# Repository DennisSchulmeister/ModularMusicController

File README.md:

Modular Music Controller
========================

<p align="center">
   <!-- https://pixabay.com/photos/screwdriver-background-screw-wooden-1008974/ -->
   
   <br>
   <b>Under Construction</b>
   <br>
   This is not yet ready for production. Many features are still missing!
   <br>
   Leave a star on GitHub and send us a message to stay updated.
</p>

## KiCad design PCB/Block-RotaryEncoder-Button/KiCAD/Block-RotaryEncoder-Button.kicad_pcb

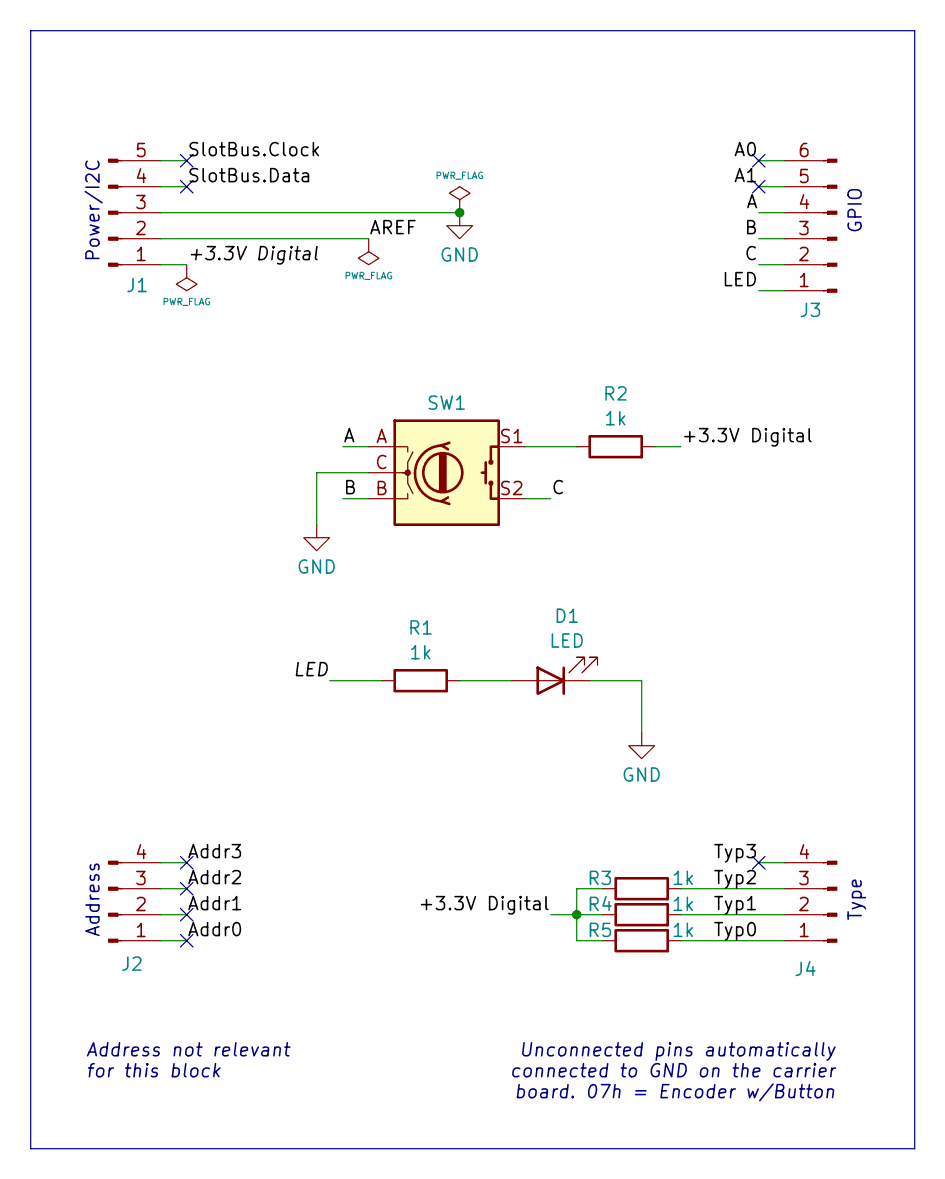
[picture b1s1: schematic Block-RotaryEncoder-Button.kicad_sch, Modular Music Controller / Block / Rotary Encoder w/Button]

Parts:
D1: LED; LED_0805_2012Metric
J1: Samtec MTMS-105-02-T-S-100; PinHeader_1x05_P1.27mm_Vertical
J2, J4: Samtec MTMS-104-02-T-S-100; PinHeader_1x04_P1.27mm_Vertical
J3: Samtec MTMS-106-02-T-S-100; PinHeader_1x06_P1.27mm_Vertical
R1, R2, R3, R4, R5: 1k; R_0402_1005Metric
SW1: CTS 11CEK25F243B; RotaryEncoder_Alps_EC11E-Switch_Vertical_H20mm

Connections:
/+3.3V Digital: J1.1, R2.2, R3.1, R4.1, R5.1
/A: J3.4, SW1.A
/A0: J3.6
/A1: J3.5
/AREF: J1.2
/Addr0: J2.1
/Addr1: J2.2
/Addr2: J2.3
/Addr3: J2.4
/B: J3.3, SW1.B
/C: J3.2, SW1.S2
/LED: J3.1, R1.1
/SlotBus.Clock: J1.5
/SlotBus.Data: J1.4
/Typ0: J4.1, R5.2
/Typ1: J4.2, R4.2
/Typ2: J4.3, R3.2
/Typ3: J4.4
GND: D1.1 (K), J1.3, SW1.C
unnamed: D1.2 (A), R1.2
unnamed: R2.1, SW1.S1

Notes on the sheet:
Unconnected pins automatically connected to GND on the carrier board. 07h = Encoder w/Button
GPIO
Type
Address not relevant for this block
Address
Power/I2C

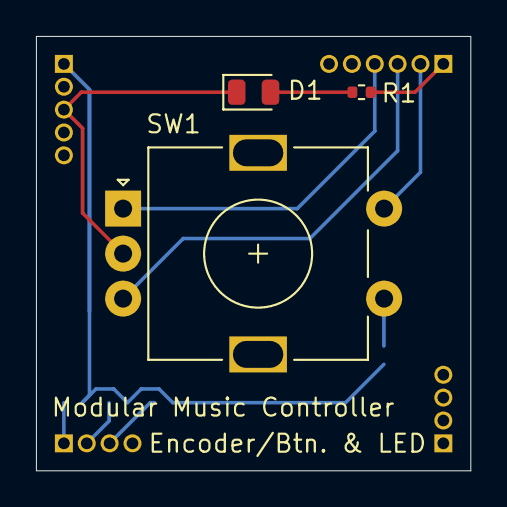
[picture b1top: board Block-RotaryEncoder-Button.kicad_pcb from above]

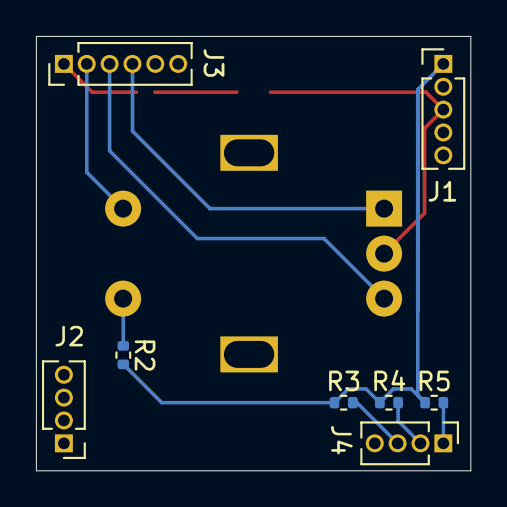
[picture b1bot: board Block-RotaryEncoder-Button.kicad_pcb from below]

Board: 2 copper layers, 24.1 x 24.1 mm, 11 parts (8 on the bottom side), 11 nets.

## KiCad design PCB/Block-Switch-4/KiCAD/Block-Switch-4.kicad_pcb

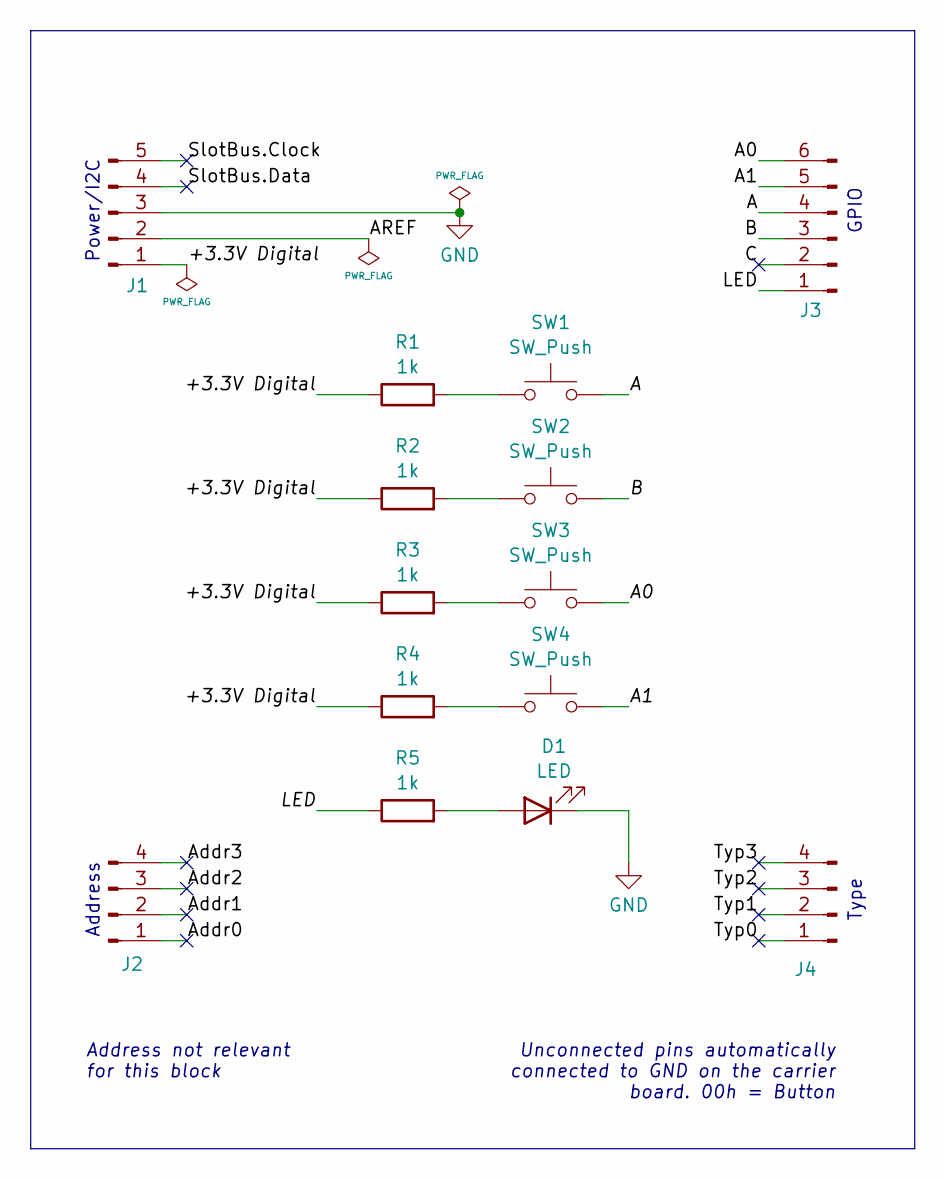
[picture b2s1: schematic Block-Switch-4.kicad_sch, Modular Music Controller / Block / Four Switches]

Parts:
D1: LED; LED_0805_2012Metric
J1: Samtec MTMS-105-02-T-S-100; PinHeader_1x05_P1.27mm_Vertical
J2, J4: Samtec MTMS-104-02-T-S-100; PinHeader_1x04_P1.27mm_Vertical
J3: Samtec MTMS-106-02-T-S-100; PinHeader_1x06_P1.27mm_Vertical
R1, R2, R3, R4, R5: 1k; R_0402_1005Metric
SW1, SW2, SW3, SW4: SW_Push; SW_PUSH_6mm

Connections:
/+3.3V Digital: J1.1, R1.1, R2.1, R3.1, R4.1
/A: J3.4, SW1.2
/A0: J3.6, SW3.2
/A1: J3.5, SW4.2
/AREF: J1.2
/Addr0: J2.1
/Addr1: J2.2
/Addr2: J2.3
/Addr3: J2.4
/B: J3.3, SW2.2
/C: J3.2
/LED: J3.1, R5.1
/SlotBus.Clock: J1.5
/SlotBus.Data: J1.4
/Typ0: J4.1
/Typ1: J4.2
/Typ2: J4.3
/Typ3: J4.4
GND: D1.1 (K), J1.3
unnamed: D1.2 (A), R5.2
unnamed: R1.2, SW1.1
unnamed: R2.2, SW2.1
unnamed: R3.2, SW3.1
unnamed: R4.2, SW4.1

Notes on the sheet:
Unconnected pins automatically connected to GND on the carrier board. 00h = Button
GPIO
Type
Address not relevant for this block
Address
Power/I2C

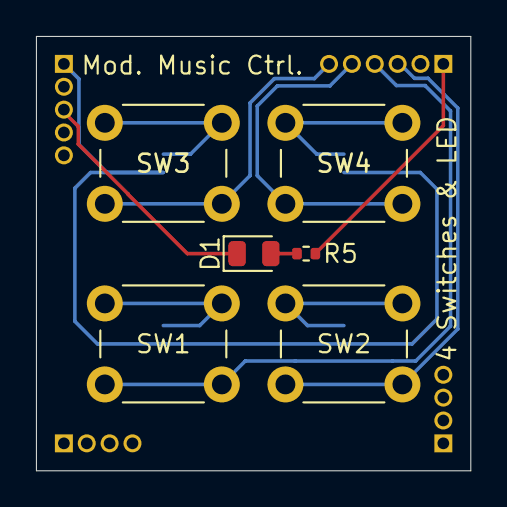
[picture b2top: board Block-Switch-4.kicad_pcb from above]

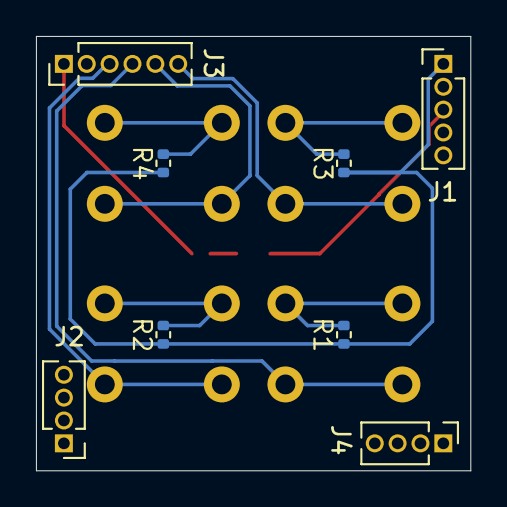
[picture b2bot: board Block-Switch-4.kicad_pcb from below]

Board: 2 copper layers, 24.1 x 24.1 mm, 14 parts (8 on the bottom side), 12 nets.

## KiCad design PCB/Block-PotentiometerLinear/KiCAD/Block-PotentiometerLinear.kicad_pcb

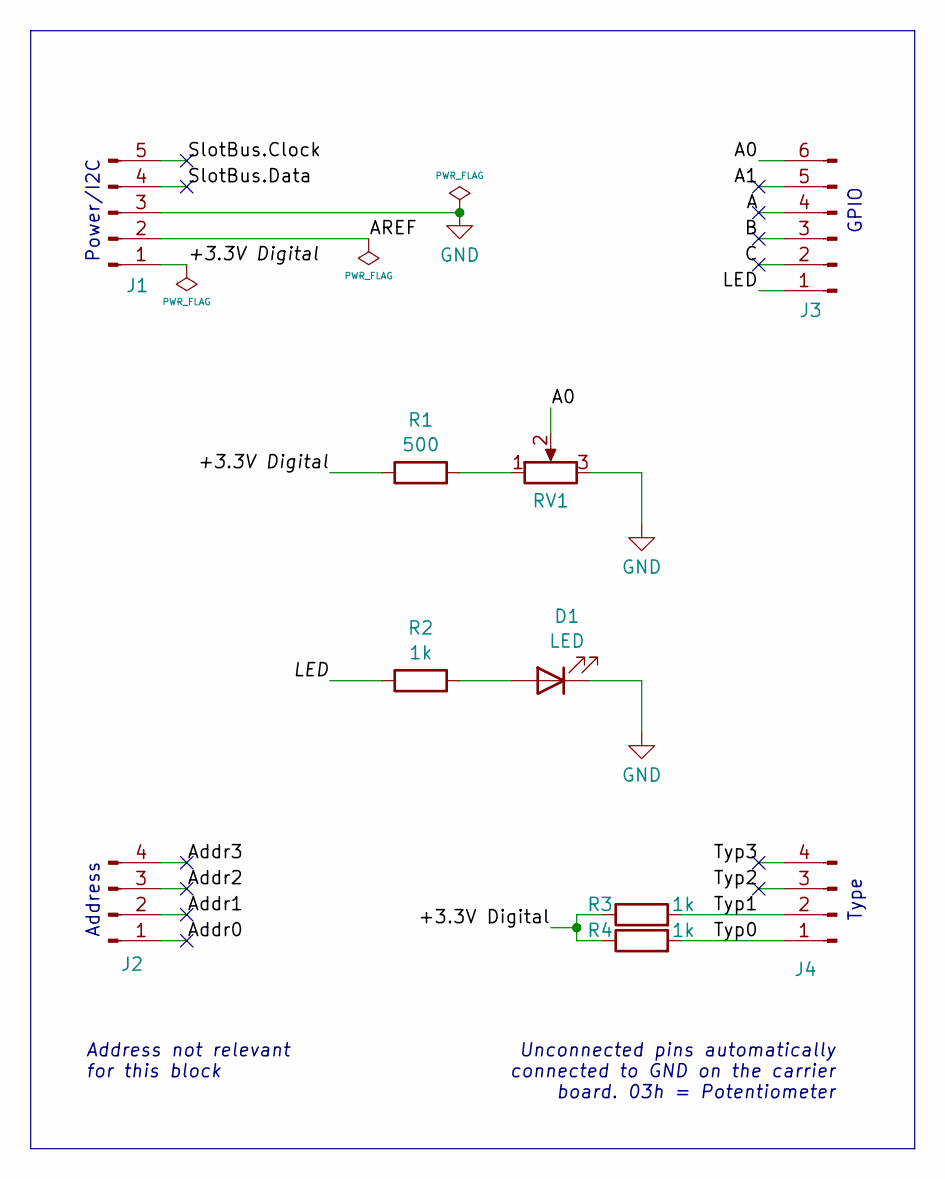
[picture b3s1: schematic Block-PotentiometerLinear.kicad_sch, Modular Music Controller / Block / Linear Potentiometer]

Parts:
D1: LED; LED_0805_2012Metric
J1: Samtec MTMS-105-02-T-S-100; PinHeader_1x05_P1.27mm_Vertical
J2, J4: Samtec MTMS-104-02-T-S-100; PinHeader_1x04_P1.27mm_Vertical
J3: Samtec MTMS-106-02-T-S-100; PinHeader_1x06_P1.27mm_Vertical
R1: 500; R_0402_1005Metric
R2, R3, R4: 1k; R_0402_1005Metric
RV1: Alps Alpine RK09D1130A1N; Potentiometer_Alps_RK09K_Single_Vertical

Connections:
/+3.3V Digital: J1.1, R1.1, R3.1, R4.1
/A: J3.4
/A0: J3.6, RV1.2
/A1: J3.5
/AREF: J1.2
/Addr0: J2.1
/Addr1: J2.2
/Addr2: J2.3
/Addr3: J2.4
/B: J3.3
/C: J3.2
/LED: J3.1, R2.1
/SlotBus.Clock: J1.5
/SlotBus.Data: J1.4
/Typ0: J4.1, R4.2
/Typ1: J4.2, R3.2
/Typ2: J4.3
/Typ3: J4.4
GND: D1.1 (K), J1.3, RV1.3
unnamed: D1.2 (A), R2.2
unnamed: R1.2, RV1.1

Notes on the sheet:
Unconnected pins automatically connected to GND on the carrier board. 03h = Potentiometer
GPIO
Type
Address not relevant for this block
Address
Power/I2C

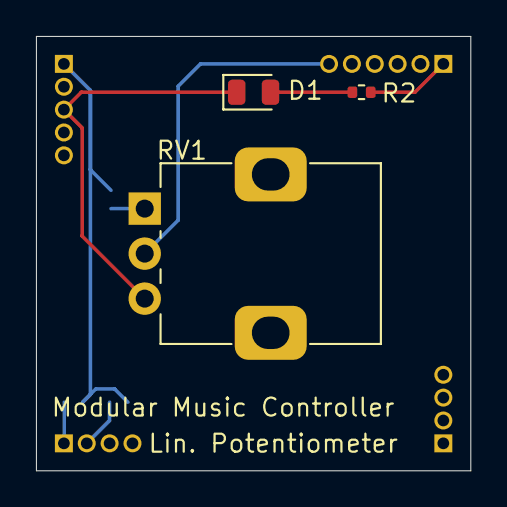
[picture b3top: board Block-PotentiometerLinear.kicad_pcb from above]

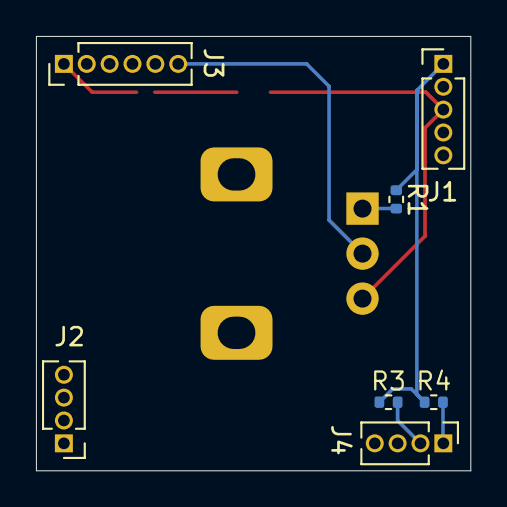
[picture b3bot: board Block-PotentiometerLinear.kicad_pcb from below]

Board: 2 copper layers, 24.1 x 24.1 mm, 10 parts (7 on the bottom side), 8 nets.

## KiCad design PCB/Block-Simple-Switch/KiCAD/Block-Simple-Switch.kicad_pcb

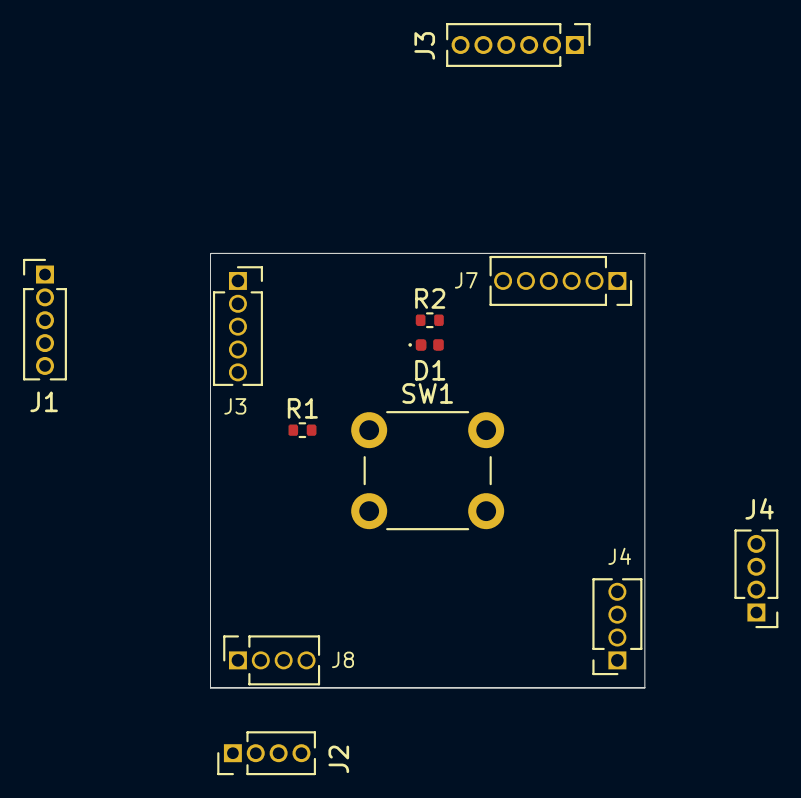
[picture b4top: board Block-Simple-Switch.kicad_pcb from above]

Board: 2 copper layers, 24.1 x 24.1 mm, 12 parts (0 on the bottom side), 6 nets, no tracks yet.

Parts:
D1: LED; LED_0402_1005Metric
J1: Samtec MTMS-105-02-T-S-100; PinHeader_1x05_P1.27mm_Vertical
J2, J4: Samtec MTMS-104-02-T-S-100; PinHeader_1x04_P1.27mm_Vertical
J3: Samtec RSM-105-02-L-S; PinSocket_1x05_P1.27mm_Vertical
J3#2: Samtec MTMS-106-02-T-S-100; PinHeader_1x06_P1.27mm_Vertical
J4#2, J8: Samtec RSM-104-02-L-S; PinSocket_1x04_P1.27mm_Vertical
J7: Samtec RSM-106-02-L-S; PinSocket_1x06_P1.27mm_Vertical
R1, R2: 1k; R_0402_1005Metric
SW1: SW_Push; SW_PUSH_6mm

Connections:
/+3.3V Digital: J1.1, R1.1
/A: J3#2.4, SW1.2
/LED: J3#2.1, R2.1
GND: D1.1 (K), J1.3, J3.3
unnamed: D1.2 (A), R2.2
unnamed: R1.2, SW1.1

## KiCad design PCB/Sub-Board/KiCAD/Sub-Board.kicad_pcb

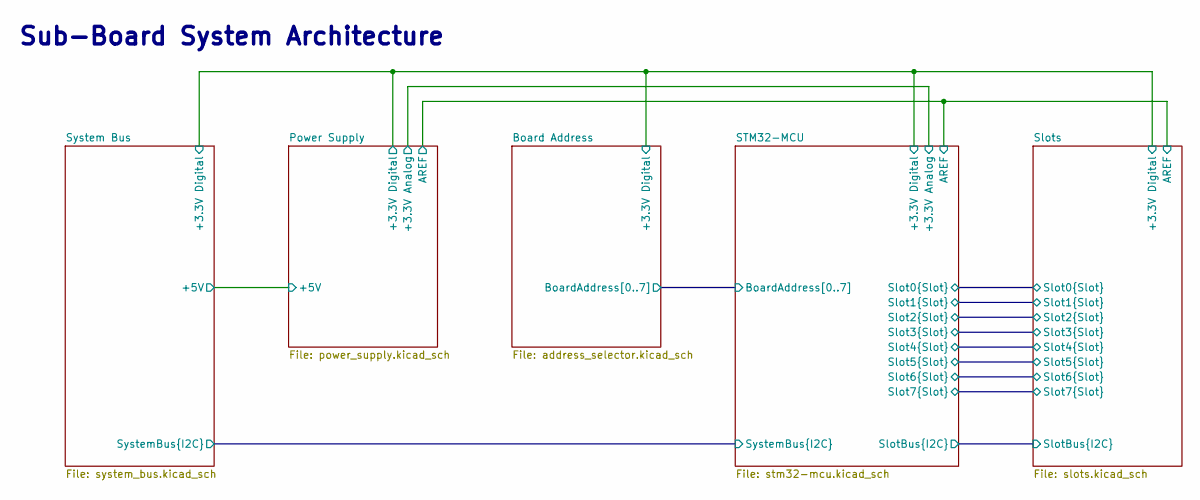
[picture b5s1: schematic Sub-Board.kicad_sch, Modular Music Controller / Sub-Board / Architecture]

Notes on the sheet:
Sub-Board System Architecture

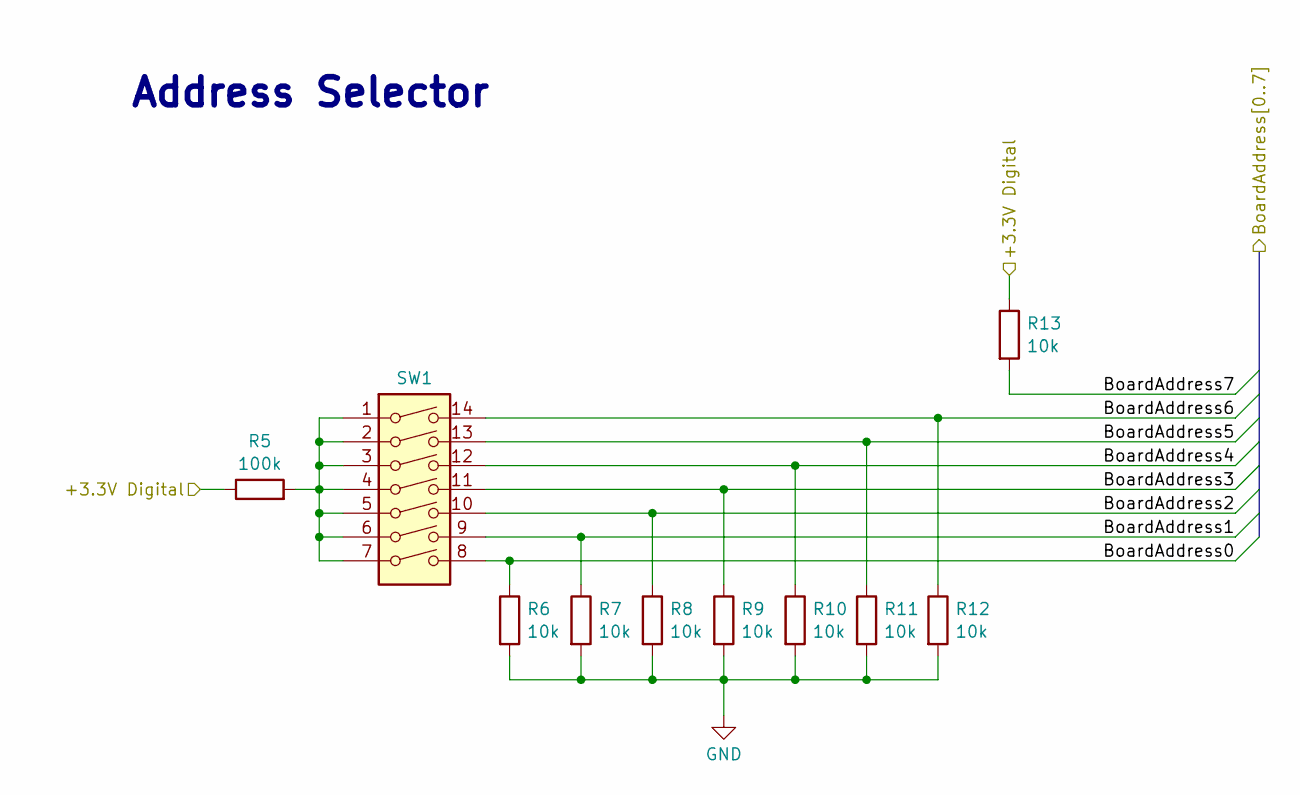
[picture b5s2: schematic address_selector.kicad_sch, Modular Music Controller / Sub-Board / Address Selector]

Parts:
R5: 100k; R_0402_1005Metric
R6, R7, R8, R9, R10, R11, R12, R13: 10k; R_0402_1005Metric
SW1: CTS 219-7LPSTR; SW_DIP_SPSTx07_Slide_6.7x19.34mm_W6.73mm_P2.54mm_LowProfile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

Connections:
/Board Address/+3.3V Digital: R5.1, R13.1; also elsewhere on the board
/Board Address/BoardAddress0: R6.1, SW1.8; also elsewhere on the board
/Board Address/BoardAddress1: R7.1, SW1.9; also elsewhere on the board
/Board Address/BoardAddress2: R8.1, SW1.10; also elsewhere on the board
/Board Address/BoardAddress3: R9.1, SW1.11; also elsewhere on the board
/Board Address/BoardAddress4: R10.1, SW1.12; also elsewhere on the board
/Board Address/BoardAddress5: R11.1, SW1.13; also elsewhere on the board
/Board Address/BoardAddress6: R12.1, SW1.14; also elsewhere on the board
/Board Address/BoardAddress7: R13.2; also elsewhere on the board
GND: R6.2, R7.2, R8.2, R9.2, R10.2, R11.2, R12.2; also elsewhere on the board
unnamed: R5.2, SW1.1, SW1.2, SW1.3, SW1.4, SW1.5, SW1.6, SW1.7

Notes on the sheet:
Address Selector

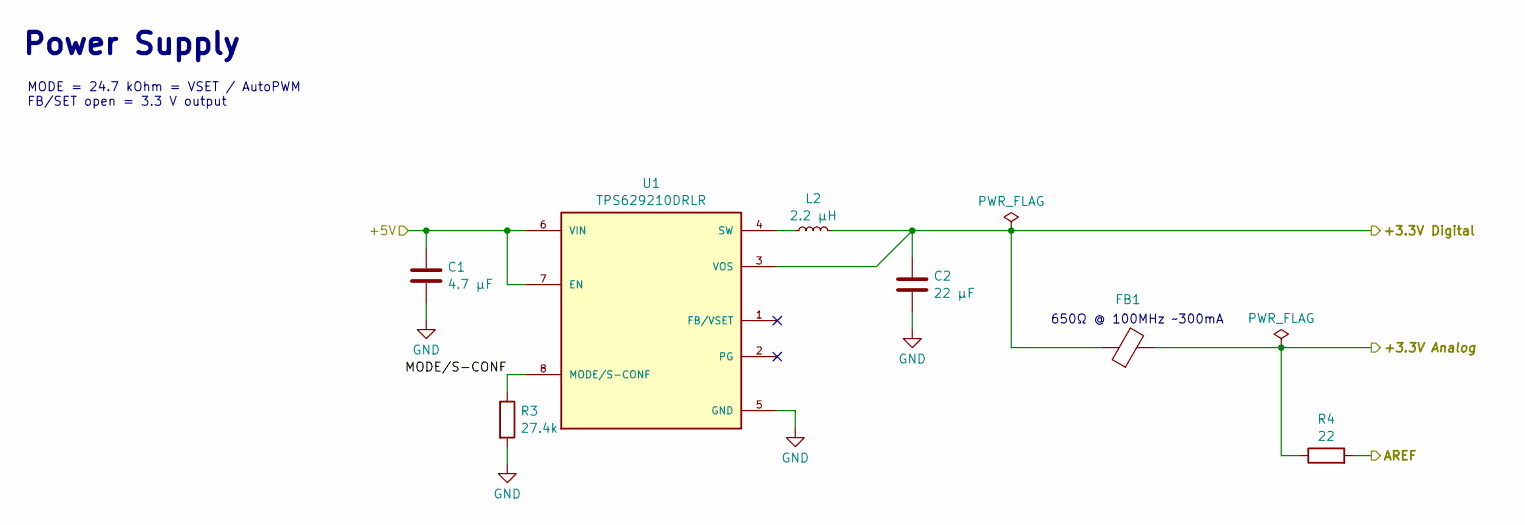
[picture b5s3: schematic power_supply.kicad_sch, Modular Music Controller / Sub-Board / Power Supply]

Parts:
C1: 4.7 µF; C_0805_2012Metric
C2: 22 µF; C_1206_3216Metric
FB1: Laird HZ0603C651R-10; L_0603_1608Metric
L2: 2.2 µH; L_0805_2012Metric
R3: 27.4k; R_0402_1005Metric
R4: 22; R_0402_1005Metric
U1: TPS629210DRLR; SOT50P160X60-8N; PARTREV B

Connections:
/Board Address/+3.3V Digital: C2.1, FB1.1, L2.2, U1.3 (VOS); also elsewhere on the board
/Power Supply/+3.3V Analog: FB1.2, R4.1; also elsewhere on the board
/Power Supply/AREF: R4.2; also elsewhere on the board
/Power Supply/MODE/S-CONF: R3.1, U1.8 (MODE/S-CONF)
/System Bus/+5V: C1.1, U1.6 (VIN), U1.7 (EN); also elsewhere on the board
GND: C1.2, C2.2, R3.2, U1.5 (GND); also elsewhere on the board
unnamed: L2.1, U1.4 (SW)

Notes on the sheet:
650Ω @ 100MHz ~300mA
Power Supply
MODE = 24.7 kOhm = VSET / AutoPWM FB/SET open = 3.3 V output

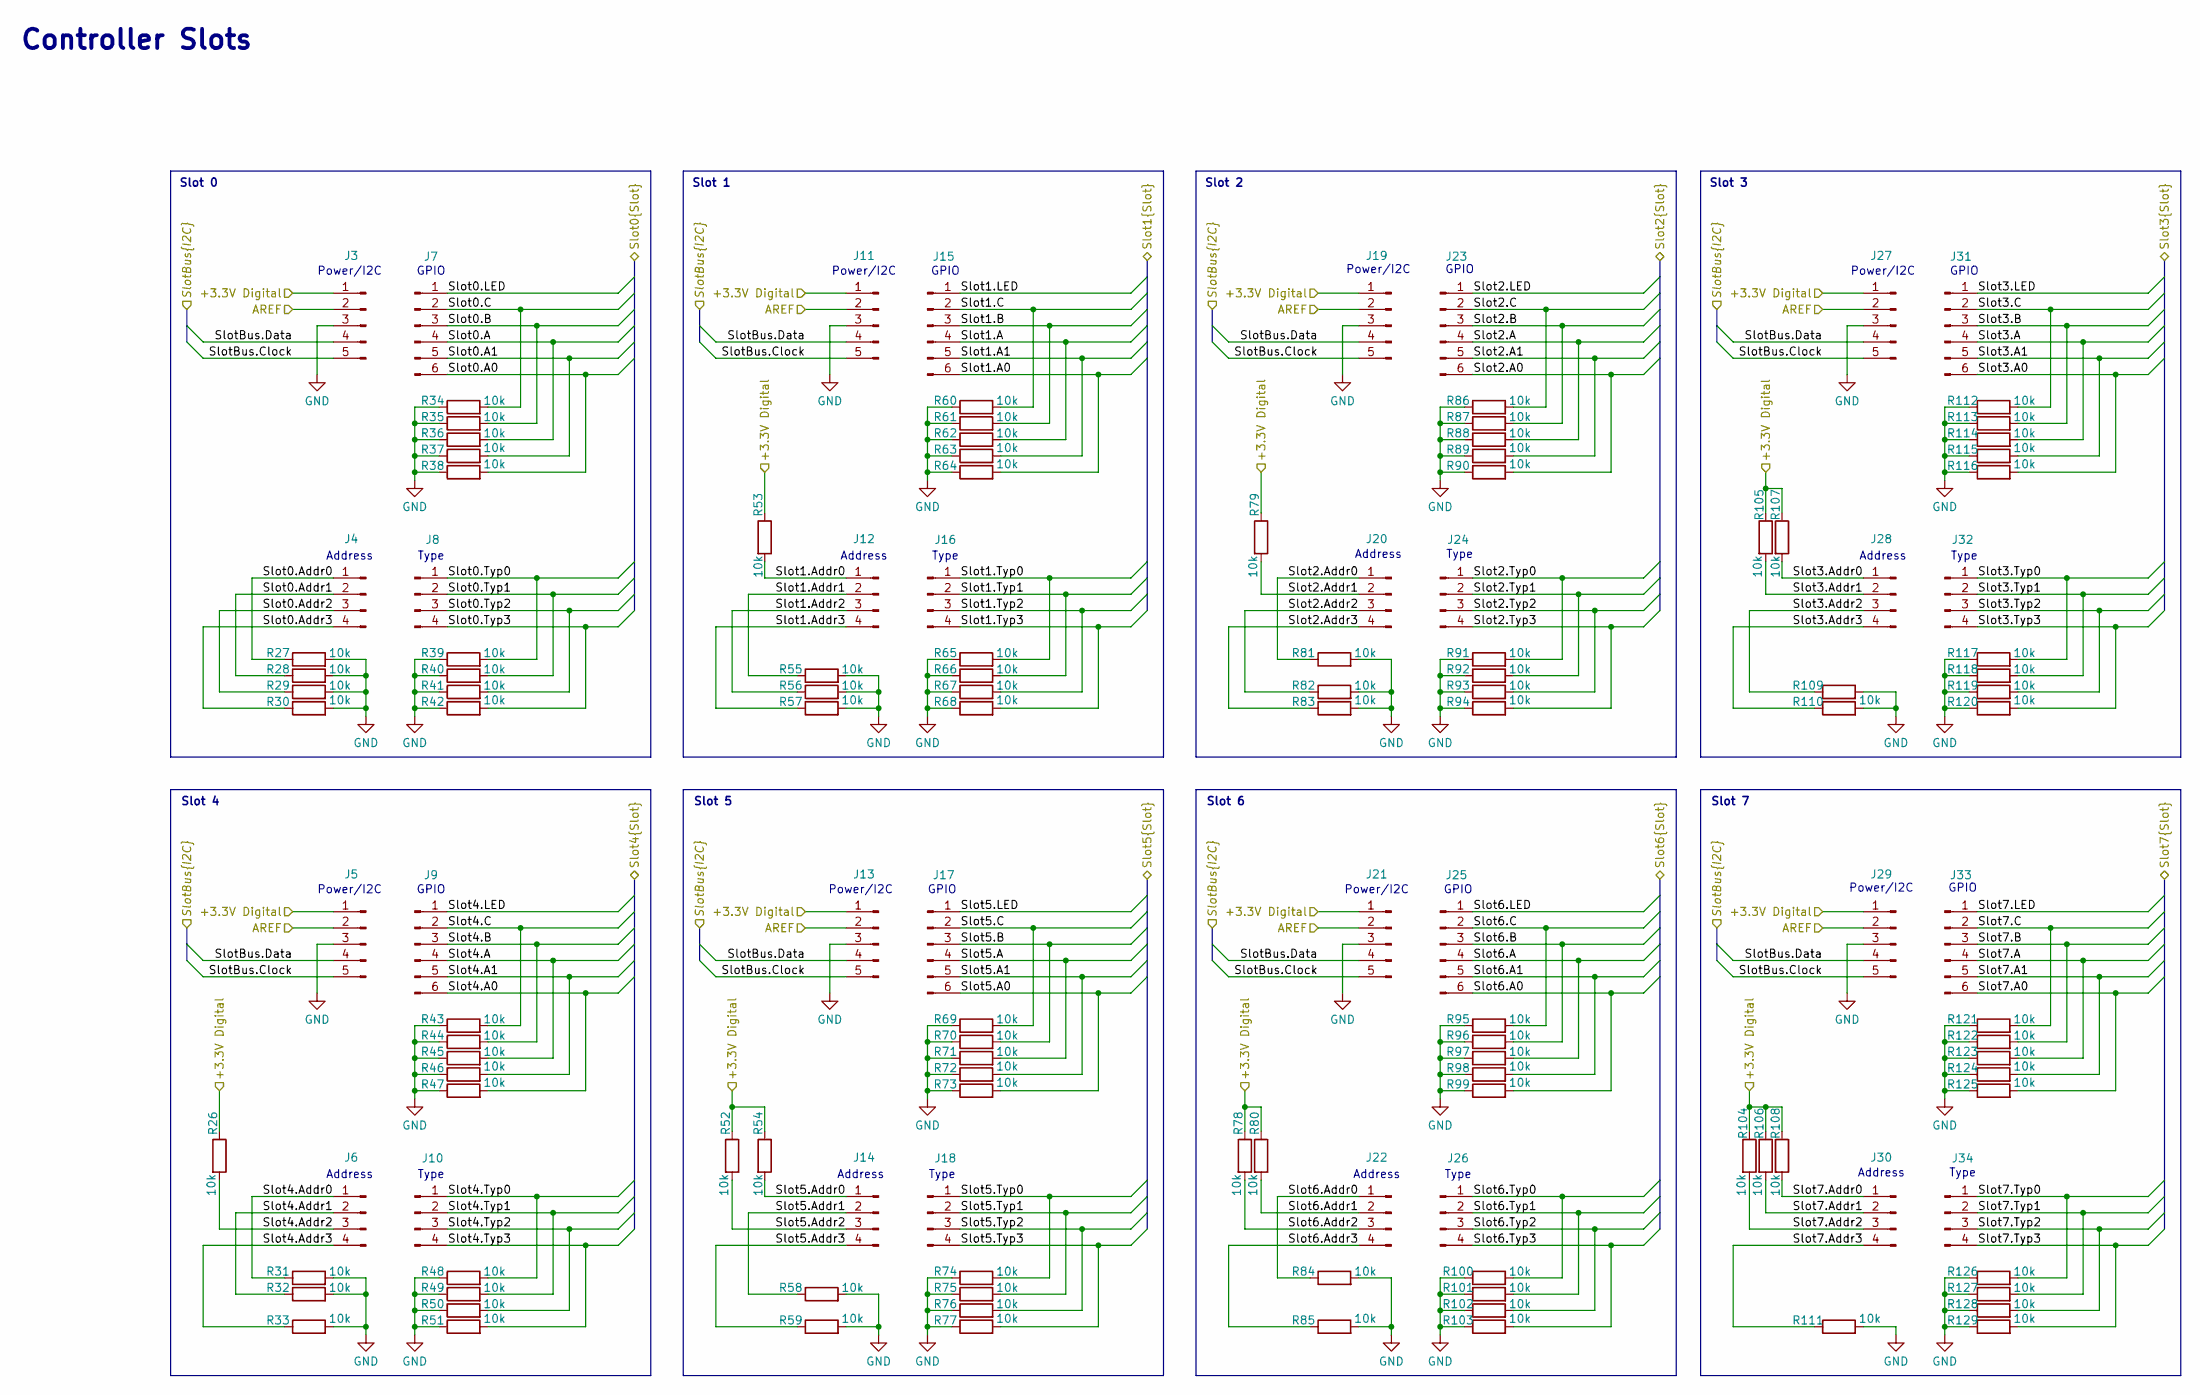
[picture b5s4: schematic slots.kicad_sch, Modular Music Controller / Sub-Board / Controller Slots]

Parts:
J3, J5, J11, J13, J19, J21, J27, J29: Samtec RSM-105-02-L-S; PinSocket_1x05_P1.27mm_Vertical
J4, J6, J8, J10, J12, J14, J16, J18, J20, J22, J24, J26, J28, J30, J32, J34: Samtec RSM-104-02-L-S; PinSocket_1x04_P1.27mm_Vertical
J7, J9, J15, J17, J23, J25, J31, J33: Samtec RSM-106-02-L-S; PinSocket_1x06_P1.27mm_Vertical
R26, R27, R28, R29, R30, R31, R32, R33, R34, R35, R36, R37, R38, R39, R40, R41, R42, R43, R44, R45, R46, R47, R48, R49, R50, R51, R52, R53, R54, R55, R56, R57, R58, R59, R60, R61, R62, R63, R64, R65, R66, R67, R68, R69, R70, R71, R72, R73, R74, R75, R76, R77, R78, R79, R80, R81, R82, R83, R84, R85, R86, R87, R88, R89, R90, R91, R92, R93, R94, R95, R96, R97, R98, R99, R100, R101, R102, R103, R104, R105, R106, R107, R108, R109, R110, R111, R112, R113, R114, R115, R116, R117, R118, R119, R120, R121, R122, R123, R124, R125, R126, R127, R128, R129: 10k; R_0402_1005Metric

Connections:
/Board Address/+3.3V Digital: J3.1, J5.1, J11.1, J13.1, J19.1, J21.1, J27.1, J29.1, R26.1, R52.1, R53.1, R54.1, R78.1, R79.1, R80.1, R104.1, R105.1, R106.1, R107.1, R108.1; also elsewhere on the board
/Power Supply/AREF: J3.2, J5.2, J11.2, J13.2, J19.2, J21.2, J27.2, J29.2; also elsewhere on the board
/STM32-MCU/Slot0.A: J7.4, R36.2; also elsewhere on the board
/STM32-MCU/Slot0.A0: J7.6, R38.2; also elsewhere on the board
/STM32-MCU/Slot0.A1: J7.5, R37.2; also elsewhere on the board
/STM32-MCU/Slot0.Addr0: J4.1, R27.1
/STM32-MCU/Slot0.Addr1: J4.2, R28.1
/STM32-MCU/Slot0.Addr2: J4.3, R29.1
/STM32-MCU/Slot0.Addr3: J4.4, R30.1
/STM32-MCU/Slot0.B: J7.3, R35.2; also elsewhere on the board
/STM32-MCU/Slot0.C: J7.2, R34.2; also elsewhere on the board
/STM32-MCU/Slot0.LED: J7.1; also elsewhere on the board
/STM32-MCU/Slot0.Typ0: J8.1, R39.2; also elsewhere on the board
/STM32-MCU/Slot0.Typ1: J8.2, R40.2; also elsewhere on the board
/STM32-MCU/Slot0.Typ2: J8.3, R41.2; also elsewhere on the board
/STM32-MCU/Slot0.Typ3: J8.4, R42.2; also elsewhere on the board
/STM32-MCU/Slot1.A: J15.4, R62.2; also elsewhere on the board
/STM32-MCU/Slot1.A0: J15.6, R64.2; also elsewhere on the board
/STM32-MCU/Slot1.A1: J15.5, R63.2; also elsewhere on the board
/STM32-MCU/Slot1.Addr0: J12.1, R53.2
/STM32-MCU/Slot1.Addr1: J12.2, R55.1
/STM32-MCU/Slot1.Addr2: J12.3, R56.1
/STM32-MCU/Slot1.Addr3: J12.4, R57.1
/STM32-MCU/Slot1.B: J15.3, R61.2; also elsewhere on the board
/STM32-MCU/Slot1.C: J15.2, R60.2; also elsewhere on the board
/STM32-MCU/Slot1.LED: J15.1; also elsewhere on the board
/STM32-MCU/Slot1.Typ0: J16.1, R65.2; also elsewhere on the board
/STM32-MCU/Slot1.Typ1: J16.2, R66.2; also elsewhere on the board
/STM32-MCU/Slot1.Typ2: J16.3, R67.2; also elsewhere on the board
/STM32-MCU/Slot1.Typ3: J16.4, R68.2; also elsewhere on the board
/STM32-MCU/Slot2.A: J23.4, R88.2; also elsewhere on the board
/STM32-MCU/Slot2.A0: J23.6, R90.2; also elsewhere on the board
/STM32-MCU/Slot2.A1: J23.5, R89.2; also elsewhere on the board
/STM32-MCU/Slot2.Addr0: J20.1, R81.1
/STM32-MCU/Slot2.Addr1: J20.2, R79.2
/STM32-MCU/Slot2.Addr2: J20.3, R82.1
/STM32-MCU/Slot2.Addr3: J20.4, R83.1
/STM32-MCU/Slot2.B: J23.3, R87.2; also elsewhere on the board
/STM32-MCU/Slot2.C: J23.2, R86.2; also elsewhere on the board
/STM32-MCU/Slot2.LED: J23.1; also elsewhere on the board
/STM32-MCU/Slot2.Typ0: J24.1, R91.2; also elsewhere on the board
/STM32-MCU/Slot2.Typ1: J24.2, R92.2; also elsewhere on the board
/STM32-MCU/Slot2.Typ2: J24.3, R93.2; also elsewhere on the board
/STM32-MCU/Slot2.Typ3: J24.4, R94.2; also elsewhere on the board
/STM32-MCU/Slot3.A: J31.4, R114.2; also elsewhere on the board
/STM32-MCU/Slot3.A0: J31.6, R116.2; also elsewhere on the board
/STM32-MCU/Slot3.A1: J31.5, R115.2; also elsewhere on the board
/STM32-MCU/Slot3.Addr0: J28.1, R107.2
/STM32-MCU/Slot3.Addr1: J28.2, R105.2
/STM32-MCU/Slot3.Addr2: J28.3, R109.1
/STM32-MCU/Slot3.Addr3: J28.4, R110.1
/STM32-MCU/Slot3.B: J31.3, R113.2; also elsewhere on the board
/STM32-MCU/Slot3.C: J31.2, R112.2; also elsewhere on the board
/STM32-MCU/Slot3.LED: J31.1; also elsewhere on the board
/STM32-MCU/Slot3.Typ0: J32.1, R117.2; also elsewhere on the board
/STM32-MCU/Slot3.Typ1: J32.2, R118.2; also elsewhere on the board
/STM32-MCU/Slot3.Typ2: J32.3, R119.2; also elsewhere on the board
/STM32-MCU/Slot3.Typ3: J32.4, R120.2; also elsewhere on the board
/STM32-MCU/Slot4.A: J9.4, R45.2; also elsewhere on the board
/STM32-MCU/Slot4.A0: J9.6, R47.2; also elsewhere on the board
/STM32-MCU/Slot4.A1: J9.5, R46.2; also elsewhere on the board
/STM32-MCU/Slot4.Addr0: J6.1, R31.1
/STM32-MCU/Slot4.Addr1: J6.2, R32.1
/STM32-MCU/Slot4.Addr2: J6.3, R26.2
/STM32-MCU/Slot4.Addr3: J6.4, R33.1
/STM32-MCU/Slot4.B: J9.3, R44.2; also elsewhere on the board
/STM32-MCU/Slot4.C: J9.2, R43.2; also elsewhere on the board
/STM32-MCU/Slot4.LED: J9.1; also elsewhere on the board
/STM32-MCU/Slot4.Typ0: J10.1, R48.2; also elsewhere on the board
/STM32-MCU/Slot4.Typ1: J10.2, R49.2; also elsewhere on the board
/STM32-MCU/Slot4.Typ2: J10.3, R50.2; also elsewhere on the board
/STM32-MCU/Slot4.Typ3: J10.4, R51.2; also elsewhere on the board
/STM32-MCU/Slot5.A: J17.4, R71.2; also elsewhere on the board
/STM32-MCU/Slot5.A0: J17.6, R73.2; also elsewhere on the board
/STM32-MCU/Slot5.A1: J17.5, R72.2; also elsewhere on the board
/STM32-MCU/Slot5.Addr0: J14.1, R54.2
/STM32-MCU/Slot5.Addr1: J14.2, R58.1
/STM32-MCU/Slot5.Addr2: J14.3, R52.2
/STM32-MCU/Slot5.Addr3: J14.4, R59.1
/STM32-MCU/Slot5.B: J17.3, R70.2; also elsewhere on the board
/STM32-MCU/Slot5.C: J17.2, R69.2; also elsewhere on the board
/STM32-MCU/Slot5.LED: J17.1; also elsewhere on the board
/STM32-MCU/Slot5.Typ0: J18.1, R74.2; also elsewhere on the board
/STM32-MCU/Slot5.Typ1: J18.2, R75.2; also elsewhere on the board
/STM32-MCU/Slot5.Typ2: J18.3, R76.2; also elsewhere on the board
/STM32-MCU/Slot5.Typ3: J18.4, R77.2; also elsewhere on the board
/STM32-MCU/Slot6.A: J25.4, R97.2; also elsewhere on the board
/STM32-MCU/Slot6.A0: J25.6, R99.2; also elsewhere on the board
/STM32-MCU/Slot6.A1: J25.5, R98.2; also elsewhere on the board
/STM32-MCU/Slot6.Addr0: J22.1, R84.1
/STM32-MCU/Slot6.Addr1: J22.2, R80.2
/STM32-MCU/Slot6.Addr2: J22.3, R78.2
/STM32-MCU/Slot6.Addr3: J22.4, R85.1
/STM32-MCU/Slot6.B: J25.3, R96.2; also elsewhere on the board
/STM32-MCU/Slot6.C: J25.2, R95.2; also elsewhere on the board
/STM32-MCU/Slot6.LED: J25.1; also elsewhere on the board
/STM32-MCU/Slot6.Typ0: J26.1, R100.2; also elsewhere on the board
/STM32-MCU/Slot6.Typ1: J26.2, R101.2; also elsewhere on the board
/STM32-MCU/Slot6.Typ2: J26.3, R102.2; also elsewhere on the board
/STM32-MCU/Slot6.Typ3: J26.4, R103.2; also elsewhere on the board
/STM32-MCU/Slot7.A: J33.4, R123.2; also elsewhere on the board
/STM32-MCU/Slot7.A0: J33.6, R125.2; also elsewhere on the board
/STM32-MCU/Slot7.A1: J33.5, R124.2; also elsewhere on the board
/STM32-MCU/Slot7.Addr0: J30.1, R108.2
/STM32-MCU/Slot7.Addr1: J30.2, R106.2
/STM32-MCU/Slot7.Addr2: J30.3, R104.2
/STM32-MCU/Slot7.Addr3: J30.4, R111.1
/STM32-MCU/Slot7.B: J33.3, R122.2; also elsewhere on the board
/STM32-MCU/Slot7.C: J33.2, R121.2; also elsewhere on the board
/STM32-MCU/Slot7.LED: J33.1; also elsewhere on the board
/STM32-MCU/Slot7.Typ0: J34.1, R126.2; also elsewhere on the board
/STM32-MCU/Slot7.Typ1: J34.2, R127.2; also elsewhere on the board
/STM32-MCU/Slot7.Typ2: J34.3, R128.2; also elsewhere on the board
/STM32-MCU/Slot7.Typ3: J34.4, R129.2; also elsewhere on the board
/STM32-MCU/SlotBus.Clock: J3.5, J5.5, J11.5, J13.5, J19.5, J21.5, J27.5, J29.5; also elsewhere on the board
/STM32-MCU/SlotBus.Data: J3.4, J5.4, J11.4, J13.4, J19.4, J21.4, J27.4, J29.4; also elsewhere on the board
GND: J3.3, J5.3, J11.3, J13.3, J19.3, J21.3, J27.3, J29.3, R27.2, R28.2, R29.2, R30.2, R31.2, R32.2, R33.2, R34.1, R35.1, R36.1, R37.1, R38.1, R39.1, R40.1, R41.1, R42.1, R43.1, R44.1, R45.1, R46.1, R47.1, R48.1, R49.1, R50.1, R51.1, R55.2, R56.2, R57.2, R58.2, R59.2, R60.1, R61.1, R62.1, R63.1, R64.1, R65.1, R66.1, R67.1, R68.1, R69.1, R70.1, R71.1, R72.1, R73.1, R74.1, R75.1, R76.1, R77.1, R81.2, R82.2, R83.2, R84.2, R85.2, R86.1, R87.1, R88.1, R89.1, R90.1, R91.1, R92.1, R93.1, R94.1, R95.1, R96.1, R97.1, R98.1, R99.1, R100.1, R101.1, R102.1, R103.1, R109.2, R110.2, R111.2, R112.1, R113.1, R114.1, R115.1, R116.1, R117.1, R118.1, R119.1, R120.1, R121.1, R122.1, R123.1, R124.1, R125.1, R126.1, R127.1, R128.1, R129.1; also elsewhere on the board

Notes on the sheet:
Type
Power/I2C
Address
Slot 6
GPIO
Slot 0
Slot 2
Slot 4
Controller Slots
Slot 1
Slot 3
Slot 5
Slot 7
